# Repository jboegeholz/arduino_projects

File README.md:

# Arduino Projekte

## LED blinken lassen
## LED mit Taster togglen
## 7-Segment-Anzeige
## Temperatur-Sensor auswerten
## Motor ansteuern
## LIDAR auswerten

https://www.rahner-edu.de/robotik/boe-shield-bot-arduino/fototransistor/

https://www.youtube.com/watch?v=vMCLmSCfkiY

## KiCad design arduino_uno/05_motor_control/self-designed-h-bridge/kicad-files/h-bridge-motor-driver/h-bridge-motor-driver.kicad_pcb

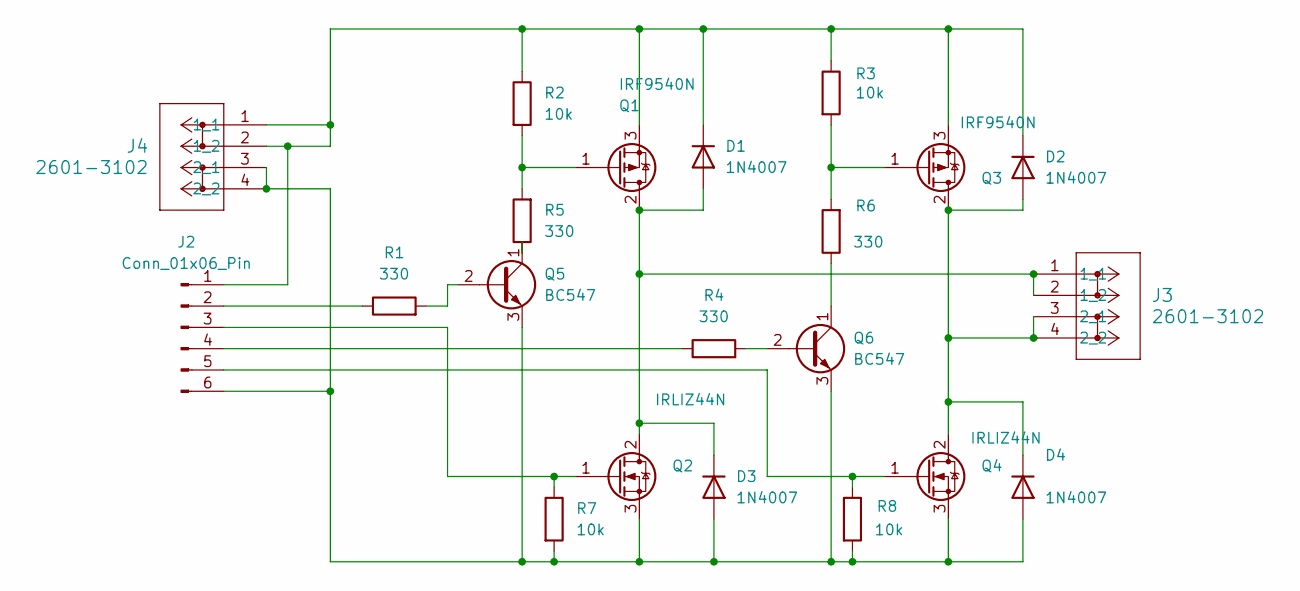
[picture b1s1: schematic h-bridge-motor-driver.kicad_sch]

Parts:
D1, D2, D3, D4: 1N4007; D_DO-41_SOD81_P10.16mm_Horizontal
J2: Conn_01x06_Pin; PinSocket_1x06_P2.54mm_Vertical
J3, J4: 2601-3102; CONN2_2601-3102_WAG
Q1, Q3: IRF9540N; TO-220-3_Vertical
Q2, Q4: IRLIZ44N; TO-220F-3_Vertical
Q5, Q6: BC547; TO-92_Inline
R1, R4, R5, R6: 330; R_Axial_DIN0207_L6.3mm_D2.5mm_P10.16mm_Horizontal
R2, R3, R7, R8: 10k; R_Axial_DIN0207_L6.3mm_D2.5mm_P10.16mm_Horizontal

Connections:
unnamed: D1.2 (A), D3.1 (K), J3.1 (1_1), J3.2 (1_2), Q1.2 (D), Q2.2 (D)
unnamed: D1.1 (K), D2.1 (K), J2.1, J4.1 (1_1), J4.2 (1_2), Q1.3 (S), Q3.3 (S), R2.1, R3.1
unnamed: D2.2 (A), D4.1 (K), J3.3 (2_1), J3.4 (2_2), Q3.2 (D), Q4.2 (D)
unnamed: D3.2 (A), D4.2 (A), J2.6, J4.3 (2_1), J4.4 (2_2), Q2.3 (S), Q4.3 (S), Q5.3 (E), Q6.3 (E), R7.2, R8.2
unnamed: J2.2, R1.1
unnamed: J2.3, Q2.1 (G), R7.1
unnamed: J2.4, R4.1
unnamed: J2.5, Q4.1 (G), R8.1
unnamed: Q1.1 (G), R2.2, R5.2
unnamed: Q3.1 (G), R3.2, R6.2
unnamed: Q5.2 (B), R1.2
unnamed: Q5.1 (C), R5.1
unnamed: Q6.2 (B), R4.2
unnamed: Q6.1 (C), R6.1

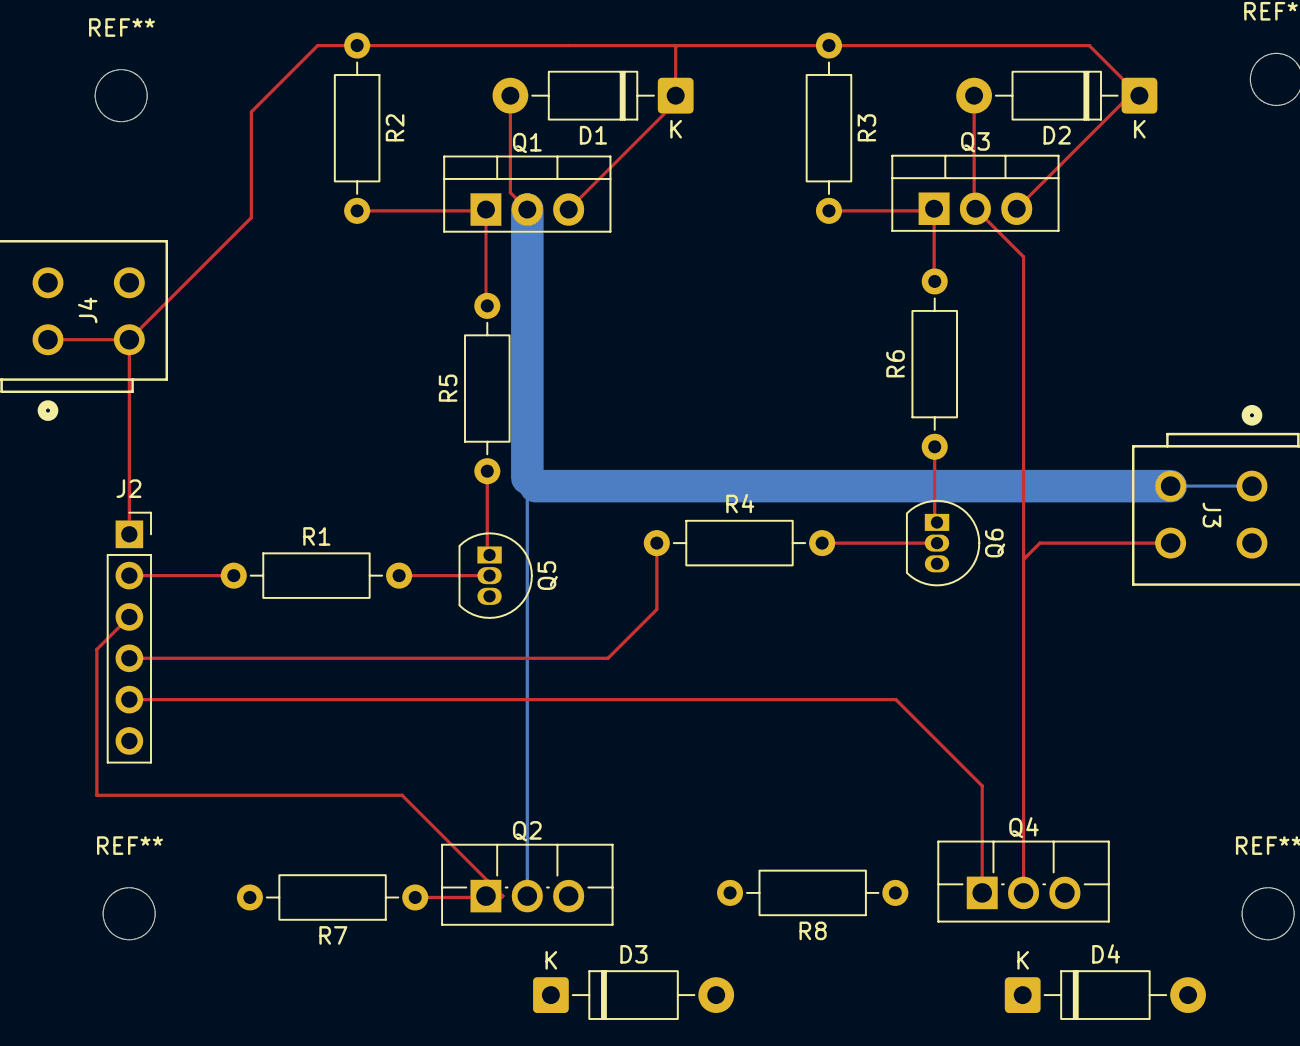
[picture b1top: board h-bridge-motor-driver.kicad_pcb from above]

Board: 2 copper layers, 21 parts (0 on the bottom side), 14 nets.

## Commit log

2017-09-11 Create seven_segment
2018-03-07 added PROGMEM
2023-11-13 rework
2023-11-22 add pwm
2023-11-29 add phototransitor
2023-12-01 add motor.ino
2023-12-10 add motor control and line follow robot
2023-12-10 add ir detector
2024-01-05 add lfr scematic add 3d printed sensor holder
2024-01-19 refactor
2024-03-29 add fritzing sketch
2024-04-28 add traffic-light.ino
2024-05-16 add bluetooth-blink.ino
2024-06-02 add funduino projects
2024-09-05 add ir-remote
2024-10-02 add oled-projects
2025-06-01 add println.ino
2025-06-06 add motor control
2025-06-07 add h-bridge.fzz
2025-06-07 route pcb
2025-06-08 add flyback diodes
2025-06-17 add arduino sketch and python program for control add images
2025-06-19 add support for arduino on macos
2025-06-19 add key bindings
2025-06-19 switch off corresponding transistor when changing directions
2025-06-25 add schematics for kicad
2025-06-26 add wago clamp
2025-06-26 rework schematic
2025-06-26 move fritzing files add footprints to parts
2025-06-26 rework pcb
2025-06-27 add 3d model to wago connector
2025-06-27 add h-bridge control logic
2025-06-29 add labels to connector
2025-06-30 add wiring
2025-07-02 add power flags / no connect
2025-07-03 start routing
